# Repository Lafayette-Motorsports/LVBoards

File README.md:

# MotorsportsLVBoards

LV Board repository for Motorsports created 09.02.2025  

## BE SURE TO COMMIT & PUSH ALL CHANGES WHEN FINISHED TO KEEP THINGS UPDATED  

## Modulation
LV Boards are now 'modulated' - this means that each board is designed to serve a single purpose so that individual circuits/functions can be easily replaced  
    This means that wires need to be obviosuly labeled with their purpose and output params/types to keep things 'open source' enough that it can be easily updated -- keep documentation (wiring diagram, code comments, standalone documentation) updated, descriptive, and accurate  

## If this is your first time
To use this and work on the board (non cmd because if you don't know this you don't need to be trying to do it on the console):  
    - make a github account   
        - you can do this with your school email or your personal but if you plan on making changes, make your screen name traceable (eg. we want to be able to know who's doing stuff)  
    - download github for desktop (https://desktop.github.com/download/) and sign in  
    - 'follow' this repository to add it to your account  
    - click current repository (top left) --> add --> clone repository --> pull origin  
    - find your file path (repository --> show in explorer) and open whatever you want  
    - if you make changes, YOU NEED TO MANUALLY UPDATE THE REPOSITORY, ALL CHANGES MADE ARE LOCAL UNTIL THIS IS DONE  
        - go back to your github app and open the repository (its probably still open), add a summary and commit your changes, push to origin  
        - MAKE YOUR SUMMARY SOMEWHAT DETAILED, YOU DON'T NEED A PARAGRAPH BUT THIS IS A REALLY GOOD PLACE TO PUT A CHANGE LOG SO WE CAN TRACK WHATS HAPPENING WHEN AND GET A SOMEWHAT DETAILED HISTORY  

## Component Cacheing
When adding parts, store them as project-specific rather than global. You will need to create your own library for the project, but you should really only need to do it once per KiCad project -- this will make sure that projects are actually portable. Some projects were built without this in mind so be weary when trying to modify/process files -- they might not have footprints/symbols for every part. If you can't figure out how to do this (or you think you added a symbol but it's not working, footprint not loading, etc.) google it or ask -- the whole point of the GitHub is portability so its kind of stupid to ignore this.

for repository admin (or other) questions - Sean McLoughlin mclougsm@lafayette.edu

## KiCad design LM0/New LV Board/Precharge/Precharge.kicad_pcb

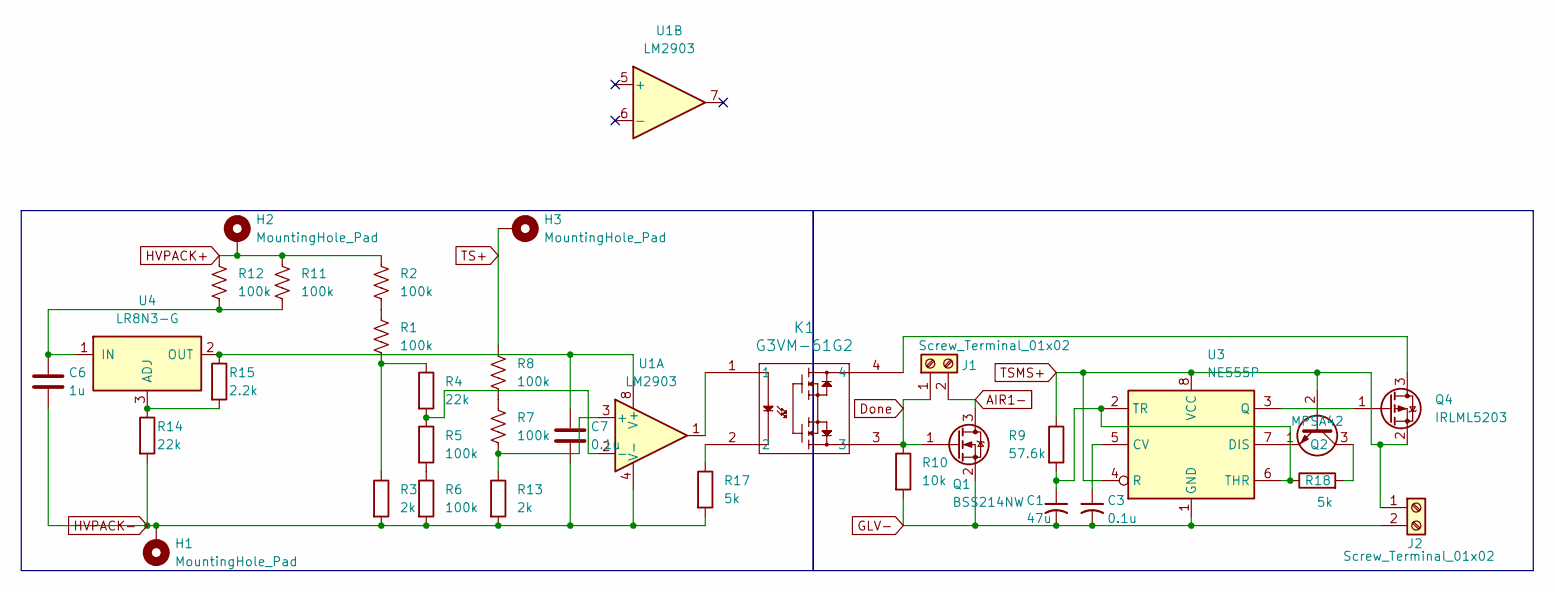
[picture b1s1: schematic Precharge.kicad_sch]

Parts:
C1: 47u; C_1210_3225Metric_Pad1.33x2.70mm_HandSolder
C3, C7: 0.1u; C_1206_3216Metric_Pad1.33x1.80mm_HandSolder
C6: 1u; C_1206_3216Metric_Pad1.33x1.80mm_HandSolder
H1, H2, H3: MountingHole_Pad; MountingHole_5.3mm_M5_DIN965_Pad
J1, J2: Screw_Terminal_01x02; TerminalBlock_MaiXu_MX126-5.0-02P_1x02_P5.00mm
K1: G3VM-61G2; G-SOP4_OMR
Q1: BSS214NW; SOT-323_SC-70_Handsoldering
Q2: MPSA42; TO-92
Q4: IRLML5203; SOT-23_Handsoldering
R1, R2, R7, R8: 100k; R_Axial_DIN0516_L15.5mm_D5.0mm_P5.08mm_Vertical
R3, R13: 2k; R_Axial_DIN0207_L6.3mm_D2.5mm_P2.54mm_Vertical
R4, R14: 22k; R_Axial_DIN0207_L6.3mm_D2.5mm_P2.54mm_Vertical
R5, R6: 100k; R_Axial_DIN0207_L6.3mm_D2.5mm_P2.54mm_Vertical
R9: 57.6k; R_Axial_DIN0207_L6.3mm_D2.5mm_P2.54mm_Vertical
R10: 10k; R_Axial_DIN0207_L6.3mm_D2.5mm_P2.54mm_Vertical
R11, R12: 100k; R_Axial_DIN0516_L15.5mm_D5.0mm_P7.62mm_Vertical
R15: 2.2k; R_Axial_DIN0207_L6.3mm_D2.5mm_P2.54mm_Vertical
R17, R18: 5k; R_Axial_DIN0207_L6.3mm_D2.5mm_P2.54mm_Vertical
U1: LM2903; DIP-8_W7.62mm
U3: NE555P; DIP-8_W7.62mm
U4: LR8N3-G; TO-92

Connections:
AIR1-: J1.2, Q1.3 (D)
Done: J1.1, K1.3, Q1.1 (G), R10.1
GLV-: C1.2, C3.2, J2.2, Q1.2 (S), R10.2, U3.1 (GND)
HVPACK+: H2.1, R2.1, R11.1, R12.1
HVPACK-: C6.2, C7.2, H1.1, R3.2, R6.2, R13.2, R14.2, R17.2, U1.4 (V-)
unnamed: K1.1, U1.1
unnamed: K1.2, R17.1
unnamed: Q2.3 (C), R18.2
unnamed: Q2.1 (E), U3.7 (DIS)
unnamed: K1.4, Q4.3 (D)
unnamed: Q4.1 (G), U3.3 (Q)
unnamed: R1.1, R2.2
unnamed: R1.2, R3.1, R4.1
unnamed: R5.2, R6.1
unnamed: R7.1, R8.2
unnamed: R7.2, R13.1, U1.3 (+)
unnamed: R4.2, R5.1, U1.2 (-)
unnamed: C7.1, R15.1, U1.8 (V+), U4.2 (OUT)
unnamed: C3.1, U3.5 (CV)
unnamed: C1.1, R9.2, R18.1, U3.2 (TR), U3.6 (THR)
unnamed: R14.1, R15.2, U4.3 (ADJ)
unnamed: C6.1, R11.2, R12.2, U4.1 (IN)
TS+: H3.1, R8.1
TSMS+: J2.1, Q2.2 (B), Q4.2 (S), R9.1, U3.4 (R), U3.8 (VCC)

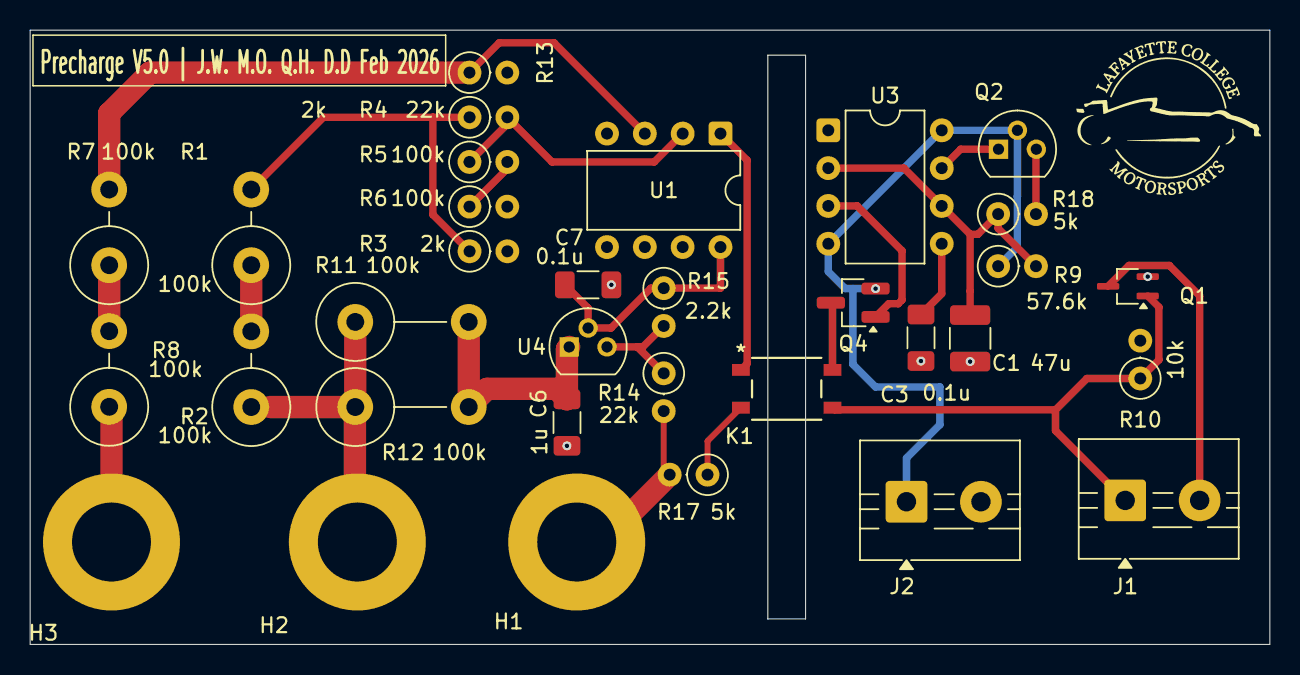
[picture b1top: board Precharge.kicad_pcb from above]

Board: 2 copper layers, 83.2 x 41.2 mm, 33 parts (0 on the bottom side), 24 nets.

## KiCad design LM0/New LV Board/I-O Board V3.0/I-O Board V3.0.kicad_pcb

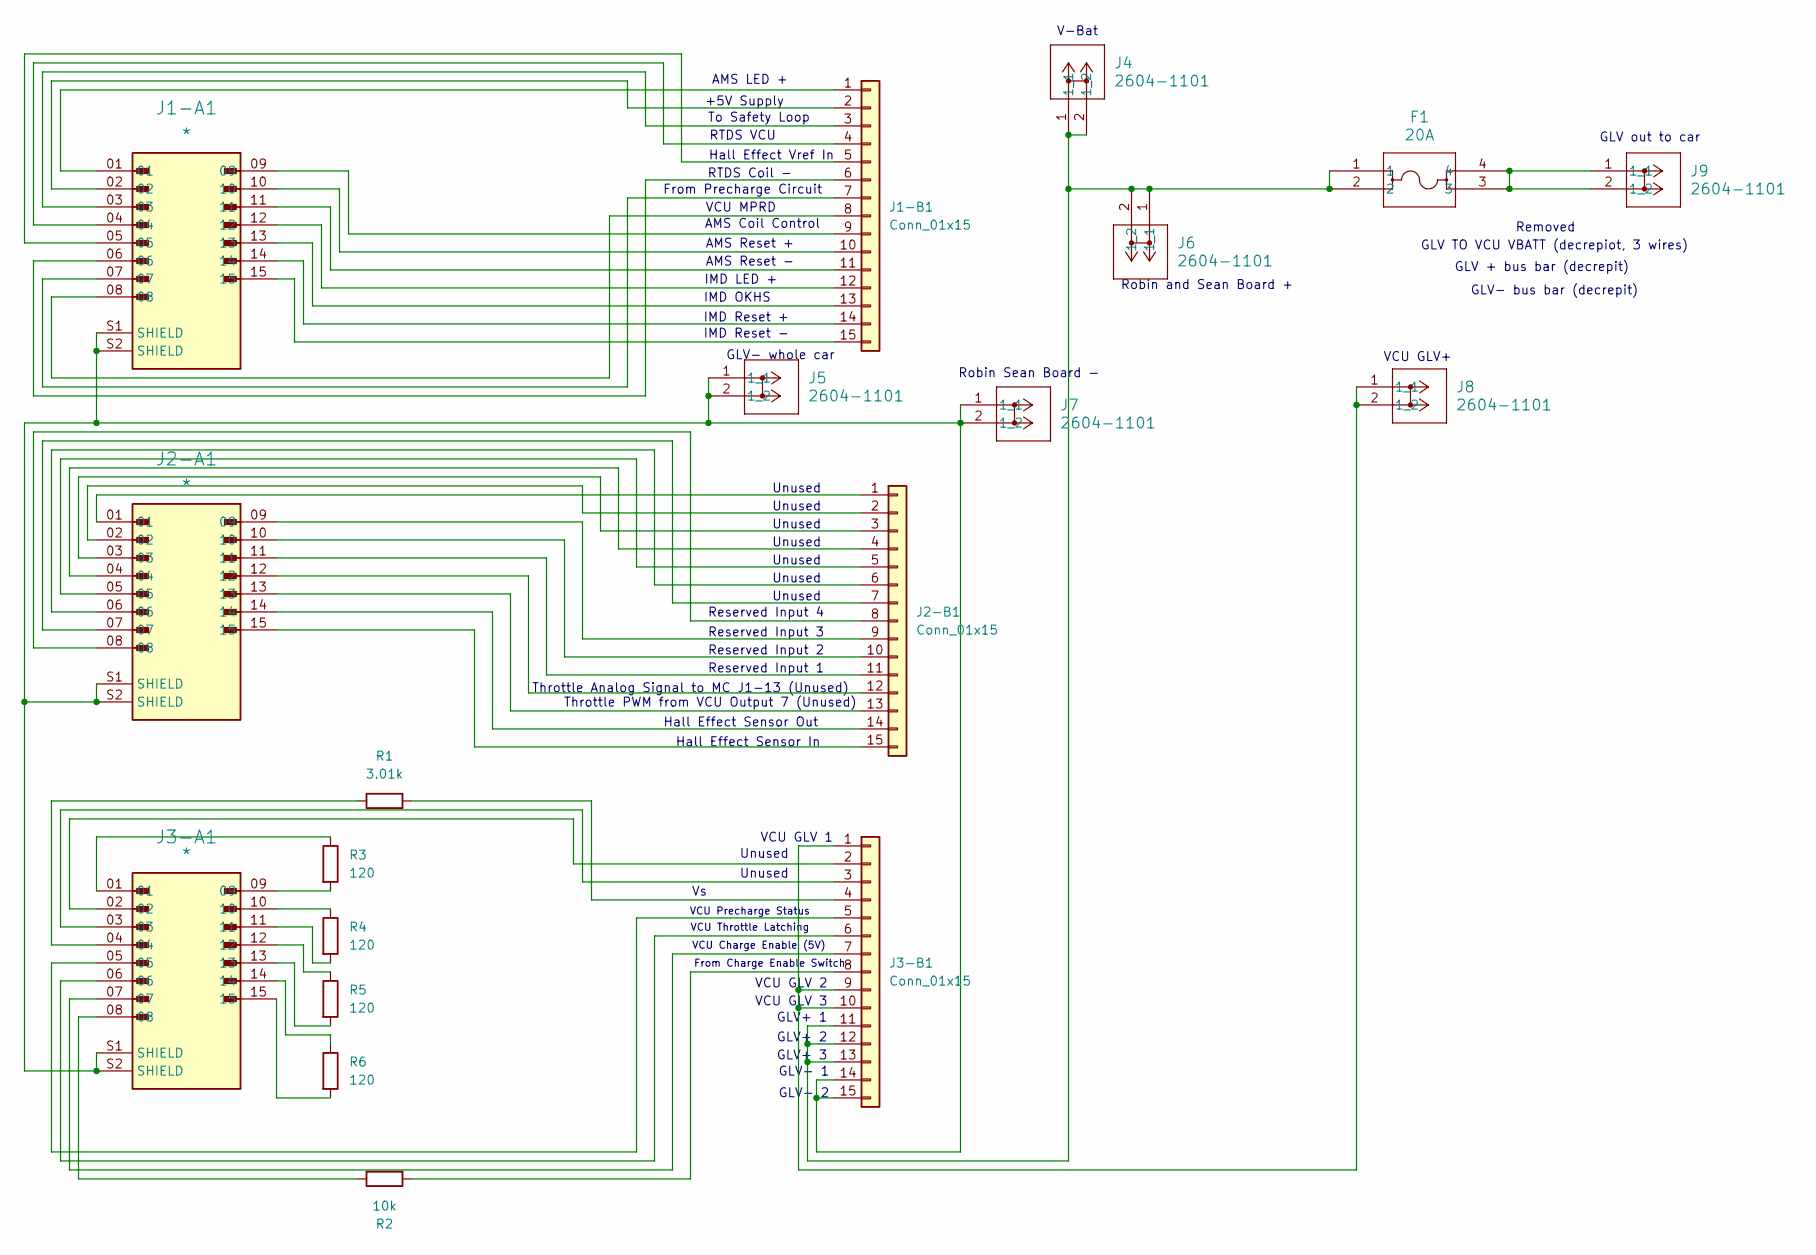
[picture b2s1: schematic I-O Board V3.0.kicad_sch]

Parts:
F1: 20A; 3568_KEY
J1-A1, J2-A1, J3-A1: *; AMPHENOL_L717SDA15P1ACH4F
J1-B1, J2-B1, J3-B1: Conn_01x15; JST_PH_B15B-PH-K_1x15_P2.00mm_Vertical
J4, J5, J6, J7, J8, J9: 2604-1101; CONN_2604-1101_WAG
R1: 3.01k; YAG_MF25_YAG
R2: 10k; YAG_MF25_YAG
R3, R4, R5, R6: 120; RESC3116X65N

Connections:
unnamed: J1-A1.01, J1-B1.1
unnamed: J1-A1.02, J1-B1.2
unnamed: J1-A1.03, J1-B1.3
unnamed: J1-A1.04, J1-B1.4
unnamed: J1-A1.05, J1-B1.5
unnamed: J1-A1.06, J1-B1.6
unnamed: J1-A1.07, J1-B1.7
unnamed: J1-A1.08, J1-B1.8
unnamed: J1-A1.09, J1-B1.9
unnamed: J1-A1.10, J1-B1.10
unnamed: J1-A1.11, J1-B1.11
unnamed: J1-A1.12, J1-B1.12
unnamed: J1-A1.13, J1-B1.13
unnamed: J1-A1.14, J1-B1.14
unnamed: J1-A1.15, J1-B1.15
unnamed: J2-A1.01, J2-B1.1
unnamed: J2-A1.02, J2-B1.2
unnamed: J2-A1.03, J2-B1.3
unnamed: J2-A1.04, J2-B1.4
unnamed: J2-A1.05, J2-B1.5
unnamed: J2-A1.06, J2-B1.6
unnamed: J2-A1.07, J2-B1.7
unnamed: J2-A1.08, J2-B1.8
unnamed: J2-A1.09, J2-B1.9
unnamed: J2-A1.10, J2-B1.10
unnamed: J2-A1.11, J2-B1.11
unnamed: J2-A1.12, J2-B1.12
unnamed: J2-A1.13, J2-B1.13
unnamed: J2-A1.14, J2-B1.14
unnamed: J2-A1.15, J2-B1.15
unnamed: J3-A1.01, R3.1
unnamed: J3-A1.04, R1.1
unnamed: J3-A1.08, R2.1
unnamed: J3-A1.09, R3.2
unnamed: J3-A1.10, R4.1
unnamed: J3-A1.11, R4.2
unnamed: J3-A1.12, R5.1
unnamed: J3-A1.13, R5.2
unnamed: J3-A1.14, R6.1
unnamed: J3-A1.15, R6.2
unnamed: J3-B1.1, J3-B1.9, J3-B1.10, J8.1, J8.2 (1)
unnamed: J3-A1.02, J3-B1.2
unnamed: J3-A1.03, J3-B1.3
unnamed: J3-B1.4, R1.2
unnamed: J3-A1.05, J3-B1.5
unnamed: J3-A1.06, J3-B1.6
unnamed: J3-A1.07, J3-B1.7
unnamed: J3-B1.8, R2.2
unnamed: F1.1, F1.2, J3-B1.11, J3-B1.12, J3-B1.13, J4.1, J4.2 (1), J6.1, J6.2 (1)
unnamed: J1-A1.S1 (SHIELD), J1-A1.S2 (SHIELD), J2-A1.S1 (SHIELD), J2-A1.S2 (SHIELD), J3-A1.S1 (SHIELD), J3-A1.S2 (SHIELD), J3-B1.14, J3-B1.15, J5.1, J5.2 (1), J7.1, J7.2 (1)
unnamed: F1.3, F1.4, J9.1, J9.2 (1)

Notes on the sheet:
V-Bat
AMS LED +
+5V Supply
VCU GLV 2
Unused
Reserved Input 2
IMD Reset -
IMD Reset +
VCU MPRD
GLV+ 3
IMD OKHS
Reserved Input 1
GLV+ 2
RTDS Coil -
VCU Charge Enable (5V)
GLV- whole car
Unused
GLV + bus bar (decrepit)
To Safety Loop
Removed
VCU GLV+
Robin Sean Board -
GLV- bus bar (decrepit)
Hall Effect Sensor Out
GLV- 1
Hall Effect Vref In
AMS Coil Control
From Charge Enable Switch
AMS Reset +
Robin and Sean Board +
GLV- 2
GLV TO VCU VBATT (decrepiot, 3 wires)
VCU GLV 1
Throttle PWM from VCU Output 7 (Unused)
Hall Effect Sensor In
VCU GLV 3
Throttle Analog Signal to MC J1-13 (Unused)
From Precharge Circuit
VCU Throttle Latching
Reserved Input 3

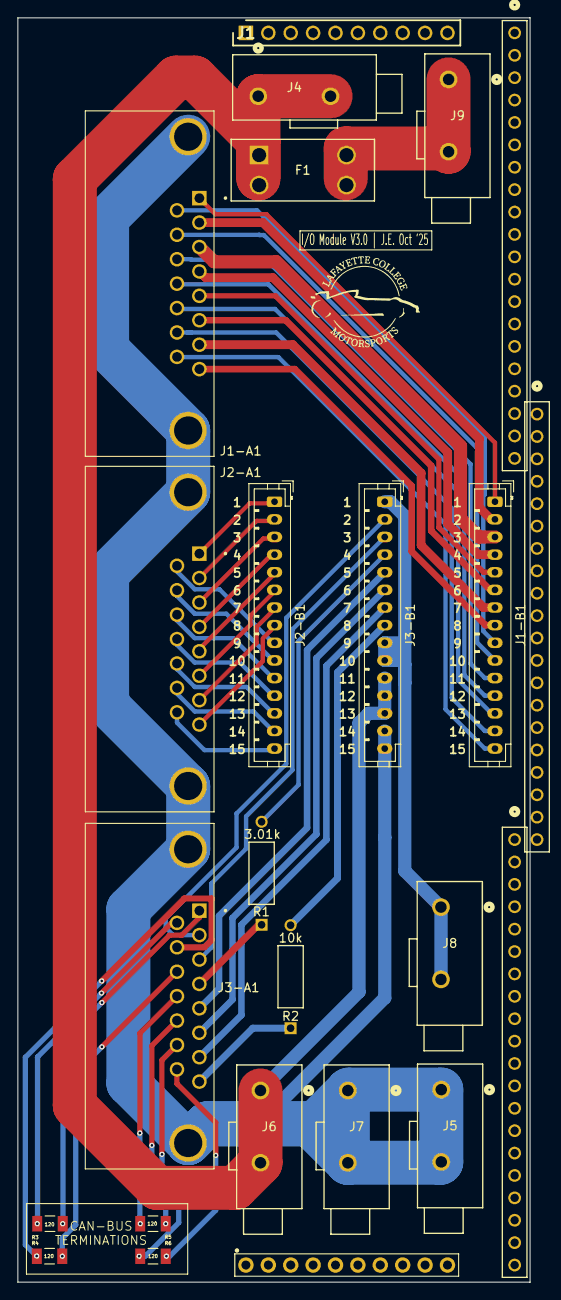
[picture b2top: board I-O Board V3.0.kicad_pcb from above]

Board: 2 copper layers, 58.1 x 143.4 mm, 24 parts (0 on the bottom side), 51 nets.

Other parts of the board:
J1: PH1-10-UA; HDRV10W64P0X254_1X10_2540X249X886P
PH2, PH2#2, PH3: 20-0600-21; CONN_20-0600-21_ARS
PH4: 1X10-2.54MM-THT

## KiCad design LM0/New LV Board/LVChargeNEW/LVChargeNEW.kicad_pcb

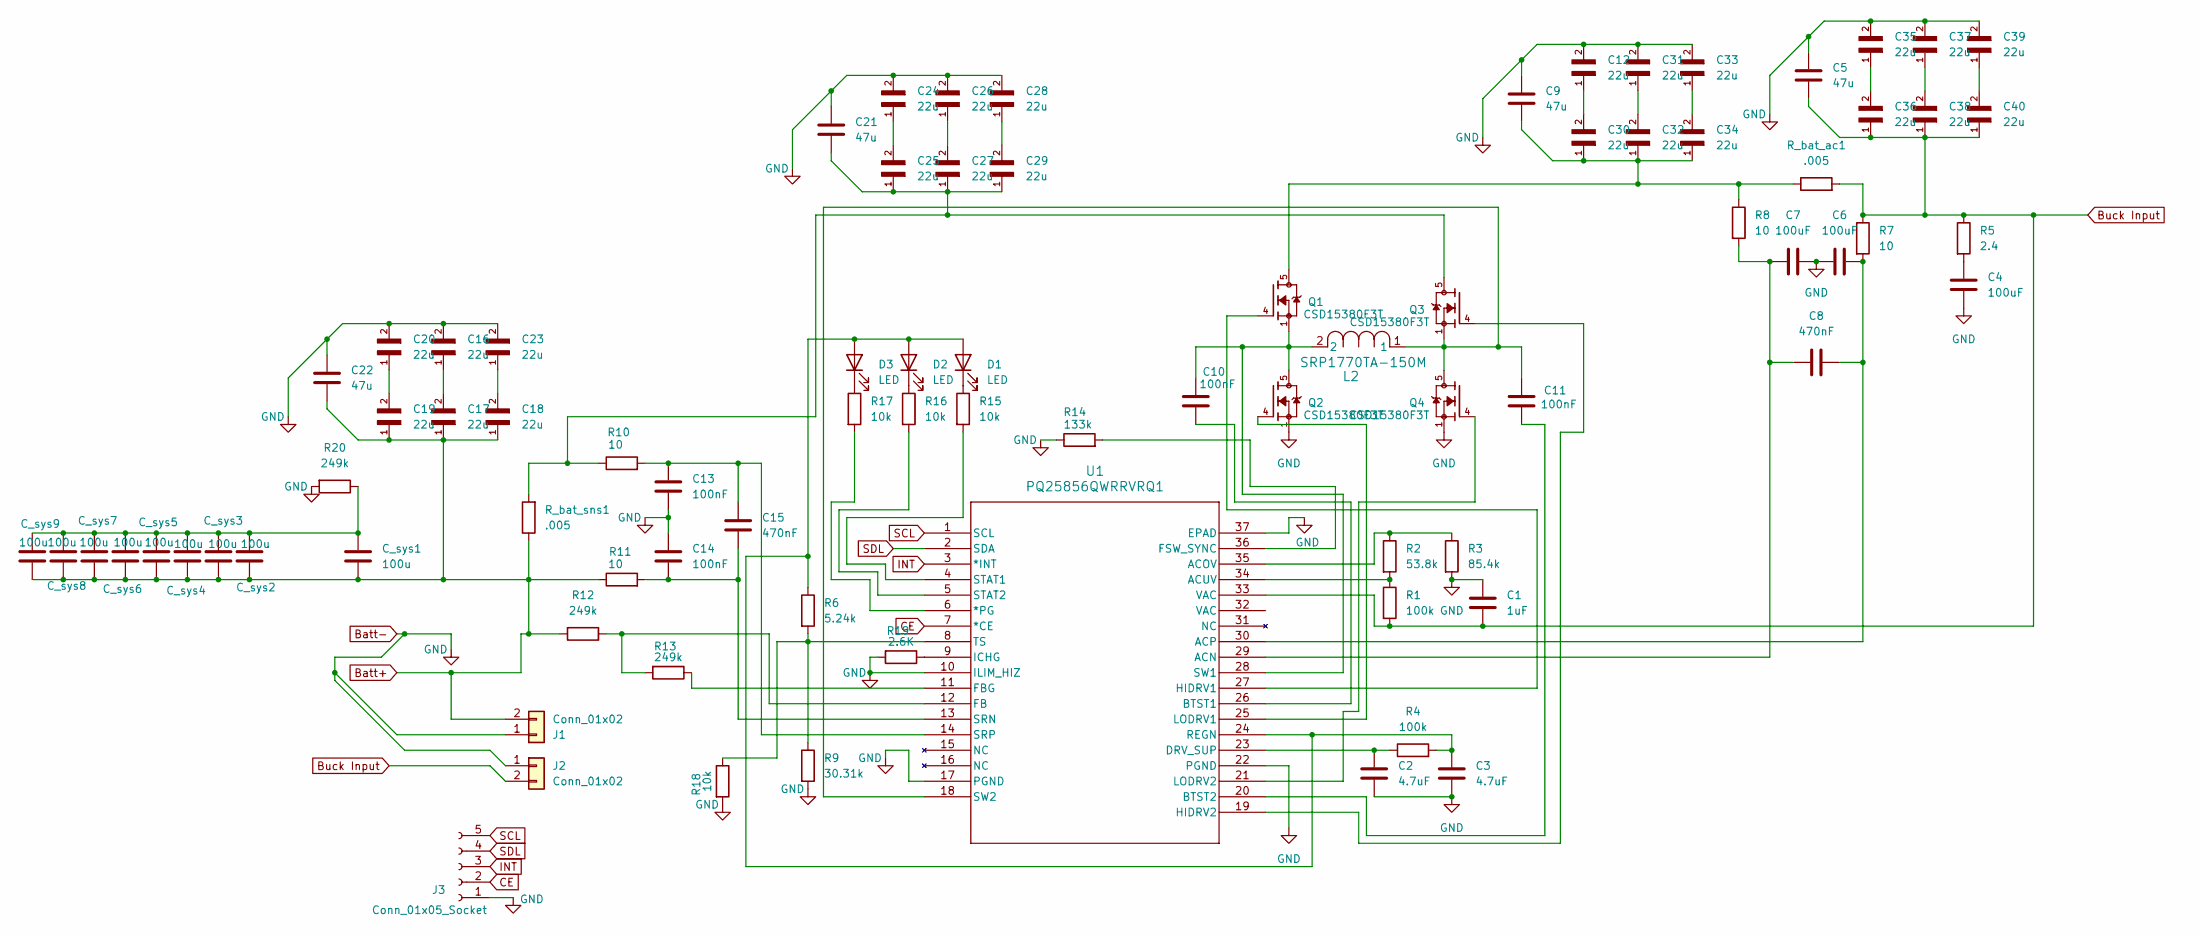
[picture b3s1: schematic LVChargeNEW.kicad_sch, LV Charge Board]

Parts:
C1: 1uF; CP_Radial_D8.0mm_P5.00mm
C2, C3: 4.7uF; CP_Radial_D8.0mm_P5.00mm
C4, C6, C7: 100uF; CP_Radial_D8.0mm_P5.00mm
C5, C9, C21, C22: 47u; C_1210_3225Metric
C8, C15: 470nF; CP_Radial_D8.0mm_P5.00mm
C10, C11, C13, C14: 100nF; CP_Radial_D8.0mm_P5.00mm
C12, C16, C17, C18, C19, C20, C23, C24, C25, C26, C27, C28, C29, C30, C31, C32, C33, C34, C35, C36, C37, C38, C39, C40: 22u; C_1210_3225Metric
C_sys1, C_sys2, C_sys3, C_sys4, C_sys5, C_sys6, C_sys7, C_sys8, C_sys9: 100u; C_1210_3225Metric_Pad1.33x2.70mm_HandSolder
D1, D2, D3: LED; LED_1206_3216Metric
J1, J2: Conn_01x02; TerminalBlock_Altech_AK300-2_P5.00mm
J3: Conn_01x05_Socket; PinSocket_1x06_P1.27mm_Vertical
L2: SRP1770TA-150M; SRP1770TA_150M
Q1, Q2, Q3, Q4: CSD15380F3T; IAUZ20N08S5L300ATMA1; PARTREV A
R1, R4: 100k; R_Axial_DIN0204_L3.6mm_D1.6mm_P5.08mm_Horizontal
R2: 53.8k; R_0805_2012Metric
R3: 85.4k; R_1206_3216Metric
R5: 2.4; R_1206_3216Metric
R6: 5.24k; R_0402_1005Metric
R7, R8, R10, R11: 10; R_1206_3216Metric_Pad1.30x1.75mm_HandSolder
R9: 30.31k; R_0805_2012Metric
R12, R13, R20: 249k; R_Axial_DIN0204_L3.6mm_D1.6mm_P5.08mm_Horizontal
R14: 133k; R_Axial_DIN0204_L3.6mm_D1.6mm_P5.08mm_Horizontal
R15, R16, R17, R18: 10k; R_Axial_DIN0204_L3.6mm_D1.6mm_P5.08mm_Horizontal
R19: 2.6K; R_0402_1005Metric_Pad0.72x0.64mm_HandSolder
R_bat_ac1: .005; RESC2012X80N
R_bat_sns1: .005; RESC2012X80N
U1: PQ25856QWRRVRQ1; Q25856QWRRVRQ1

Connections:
Batt+: C17.1, C18.1, C19.1, C22.2, C_sys1.2, C_sys2.2, C_sys3.2, C_sys4.2, C_sys5.2, C_sys6.2, C_sys7.2, C_sys8.2, C_sys9.2, J1.2, R11.1, R12.2, R_bat_sns1.1
Batt-: C1.1, C2.2, C3.2, C4.2, C5.1, C6.1, C7.2, C9.1, C12.2, C13.2, C14.1, C16.2, C20.2, C21.1, C22.1, C23.2, C24.2, C26.2, C28.2, C31.2, C33.2, C35.2, C37.2, C39.2, J1.1, J2.1, J3.1, Q2.1, Q4.1, R3.2, R9.2, R14.1, R18.2, R19.2, R20.2, U1.10 (ILIM_HIZ), U1.17 (PGND), U1.22 (PGND), U1.37 (EPAD)
Buck Input: C1.2, C5.2, C36.1, C38.1, C40.1, J2.2, R1.2, R5.1, R7.1, R_bat_ac1.2, U1.33 (VAC)
CE: J3.2, U1.7 (*CE)
INT: J3.3, U1.3 (*INT)
unnamed: C4.1, R5.2
unnamed: C12.1, C30.2
unnamed: C16.1, C17.2
unnamed: C18.2, C23.1
unnamed: C19.2, C20.1
unnamed: C21.2, C25.1, C27.1, C29.1, Q3.5, R10.1, R_bat_sns1.2
unnamed: C24.1, C25.2
unnamed: C26.1, C27.2
unnamed: C28.1, C29.2
unnamed: C9.2, C30.1, C32.1, C34.1, Q1.5, R8.1, R_bat_ac1.1
unnamed: C31.1, C32.2
unnamed: C33.1, C34.2
unnamed: C35.1, C36.2
unnamed: C37.1, C38.2
unnamed: C39.1, C40.2
unnamed: C_sys1.1, C_sys2.1, C_sys3.1, C_sys4.1, C_sys5.1, C_sys6.1, C_sys7.1, C_sys8.1, C_sys9.1, R20.1
unnamed: C3.1, D1.2 (A), D2.2 (A), D3.2 (A), R4.2, R6.1, U1.24 (REGN)
unnamed: D1.1 (K), R15.1
unnamed: D2.1 (K), R16.1
unnamed: D3.1 (K), R17.1
unnamed: R17.2, U1.6 (*PG)
unnamed: C7.1, C8.1, R8.2, U1.29 (ACN)
unnamed: R2.1, R3.1, U1.35 (ACOV)
unnamed: C6.2, C8.2, R7.2, U1.30 (ACP)
unnamed: R1.1, R2.2, U1.34 (ACUV)
unnamed: C10.1, U1.26 (BTST1)
unnamed: C11.1, U1.20 (BTST2)
unnamed: C2.1, R4.1, U1.23 (DRV_SUP)
unnamed: R12.1, R13.2, U1.12 (FB)
unnamed: R13.1, U1.11 (FBG)
unnamed: R14.2, U1.36 (FSW_SYNC)
unnamed: Q1.4, U1.27 (HIDRV1)
unnamed: Q3.4, U1.19 (HIDRV2)
unnamed: R19.1, U1.9 (ICHG)
unnamed: Q2.4, U1.25 (LODRV1)
unnamed: Q4.4, U1.21 (LODRV2)
unnamed: C14.2, C15.2, R11.2, U1.13 (SRN)
unnamed: C13.1, C15.1, R10.2, U1.14 (SRP)
unnamed: R15.2, U1.4 (STAT1)
unnamed: R16.2, U1.5 (STAT2)
unnamed: C10.2, L2.2, Q1.1, Q2.5, U1.28 (SW1)
unnamed: C11.2, L2.1, Q3.1, Q4.5, U1.18 (SW2)
unnamed: R6.2, R9.1, R18.1, U1.8 (TS)
SCL: J3.5, U1.1 (SCL)
SDL: J3.4, U1.2 (SDA)

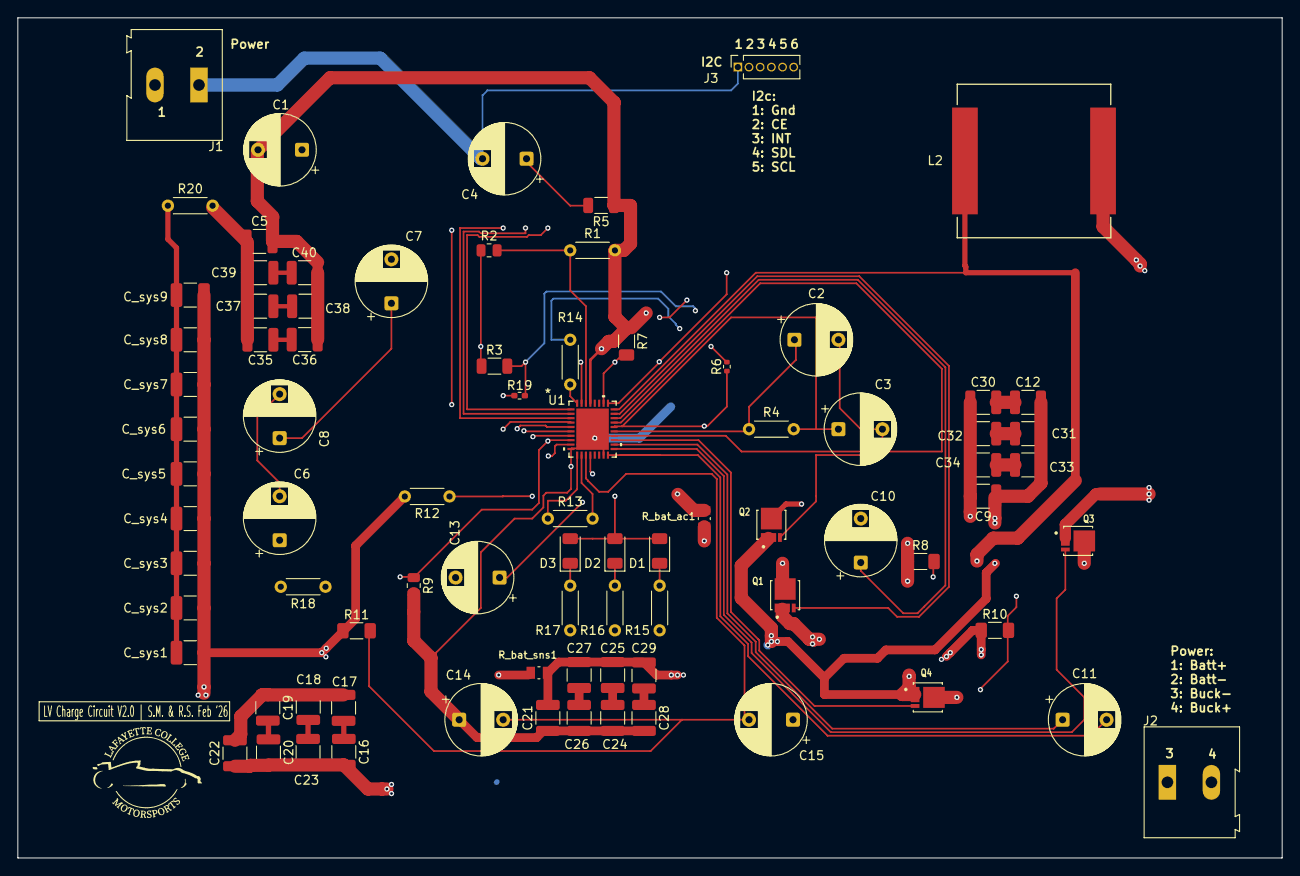
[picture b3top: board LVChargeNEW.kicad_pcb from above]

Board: 4 copper layers, 143.7 x 95.5 mm, 83 parts (0 on the bottom side), 50 nets.

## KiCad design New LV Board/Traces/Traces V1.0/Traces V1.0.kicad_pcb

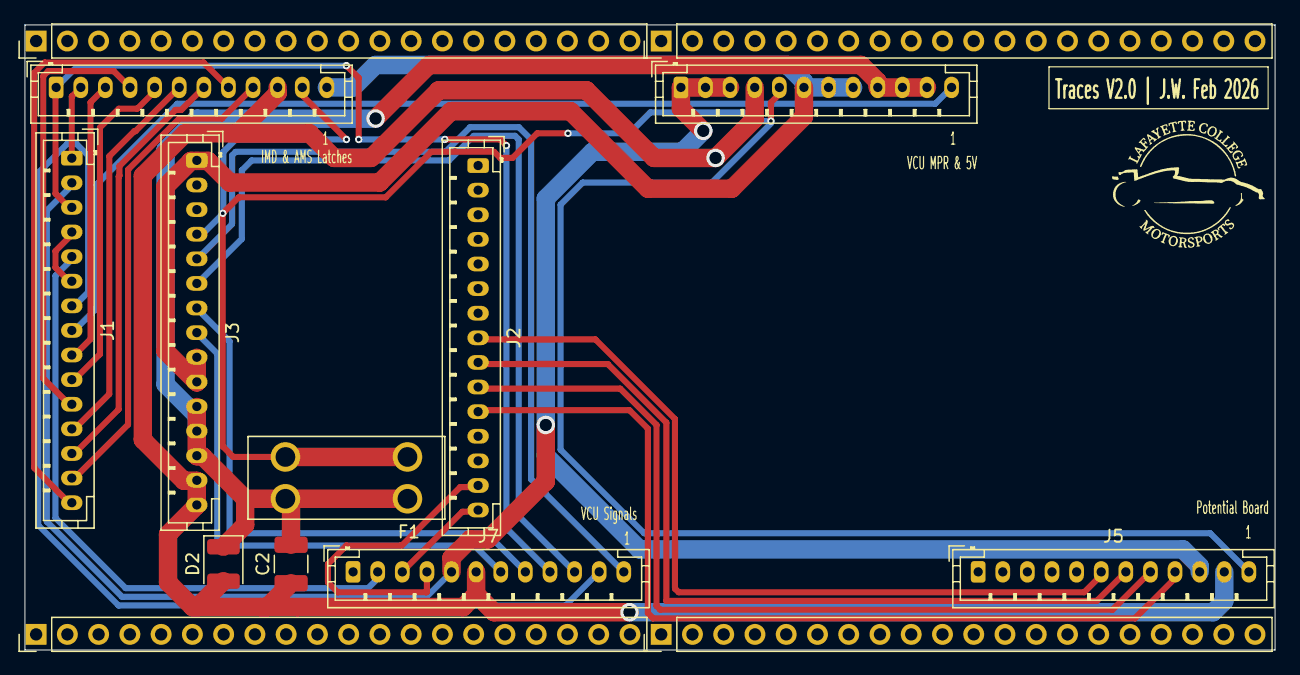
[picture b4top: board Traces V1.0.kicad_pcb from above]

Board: 2 copper layers, 101.6 x 50.8 mm, 10 parts (0 on the bottom side), 28 nets.

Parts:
C2: 47u; C_1210_3225Metric_Pad1.33x2.70mm_HandSolder
D2: D_Zener; D_1210_3225Metric
F1: 2A; FUSE_3568
J1, J2, J3: B15B-PH-K-S; JST_PH_B15B-PH-K_1x15_P2.00mm_Vertical
J4, J5, J6, J7: B12B-PH-K-S; JST_PH_B12B-PH-K_1x12_P2.00mm_Vertical

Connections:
unnamed: C2.1, D2.2 (A), J3.1, J3.2, J4.4, J5.11, J6.10, J7.6
unnamed: C2.2, D2.1 (K), F1.1, F1.2, J3.3, J3.4, J3.5, J4.9, J4.10, J4.11
unnamed: J1.10, J1.12
unnamed: J1.14, J4.1, J4.2, J4.3, J5.10, J7.5
unnamed: F1.3, F1.4, J3.12, J4.5, J5.12, J6.11
unnamed: J3.6, J3.7, J3.15, J4.6, J4.7, J4.8, J6.12
unnamed: J1.8, J4.12
unnamed: J2.8, J5.6
unnamed: J2.7, J5.7
unnamed: J2.6, J5.8
unnamed: J2.5, J5.9
unnamed: J1.13, J6.1, J7.9
unnamed: J1.15, J6.2
unnamed: J1.7, J6.3
unnamed: J1.5, J6.4
unnamed: J1.6, J6.5
unnamed: J1.4, J6.6
unnamed: J1.3, J6.7
unnamed: J1.1, J6.8
unnamed: J1.2, J6.9
unnamed: J1.11, J7.2
unnamed: J2.1, J7.3
unnamed: J2.2, J7.4
unnamed: J3.8, J7.7
unnamed: J3.9, J7.8
unnamed: J3.10, J7.10
unnamed: J1.9, J7.11
unnamed: J3.11, J7.12

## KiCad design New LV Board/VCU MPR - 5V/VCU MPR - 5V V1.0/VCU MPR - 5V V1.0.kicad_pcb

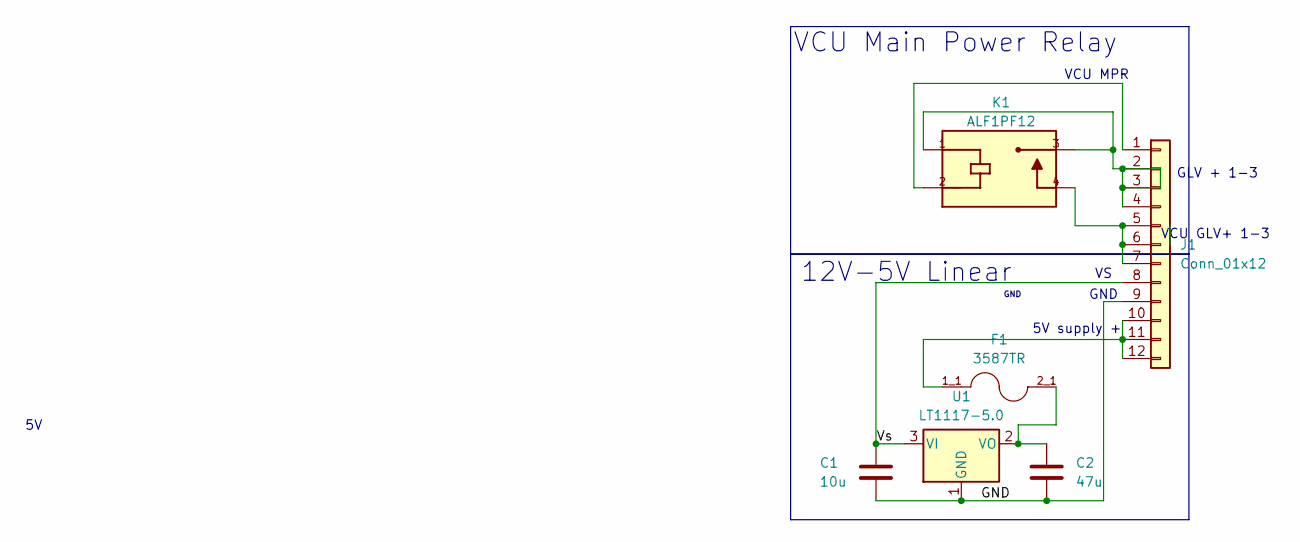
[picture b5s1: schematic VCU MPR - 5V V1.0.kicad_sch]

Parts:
C1: 10u; CAPC3225X270N
C2: 47u; CAPC3225X270N
F1: 3587TR; FUSE_3587; PARTREV D
J1: Conn_01x12; JST_PH_B12B-PH-K_1x12_P2.00mm_Vertical
K1: ALF1PF12; RELAY_ALF1PF12; DigiKey_Part_Number 255-4094-ND
U1: LT1117-5.0; REG_LT1117CST-5_TRPBF

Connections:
/GND: C1.2, C2.2, J1.9, U1.1 (GND)
/Vs: C1.1, J1.8, U1.3 (VI)
unnamed: J1.1, K1.2
unnamed: J1.2, J1.3, J1.4, K1.1, K1.3
unnamed: J1.5, J1.6, J1.7, K1.4
unnamed: F1.1_1, J1.10, J1.11, J1.12
unnamed: C2.1, F1.2_1, U1.2 (VO)

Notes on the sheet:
VCU Main Power Relay
12V-5V Linear
VCU MPR
GLV + 1-3
GND
5V supply +
VCU GLV+ 1-3

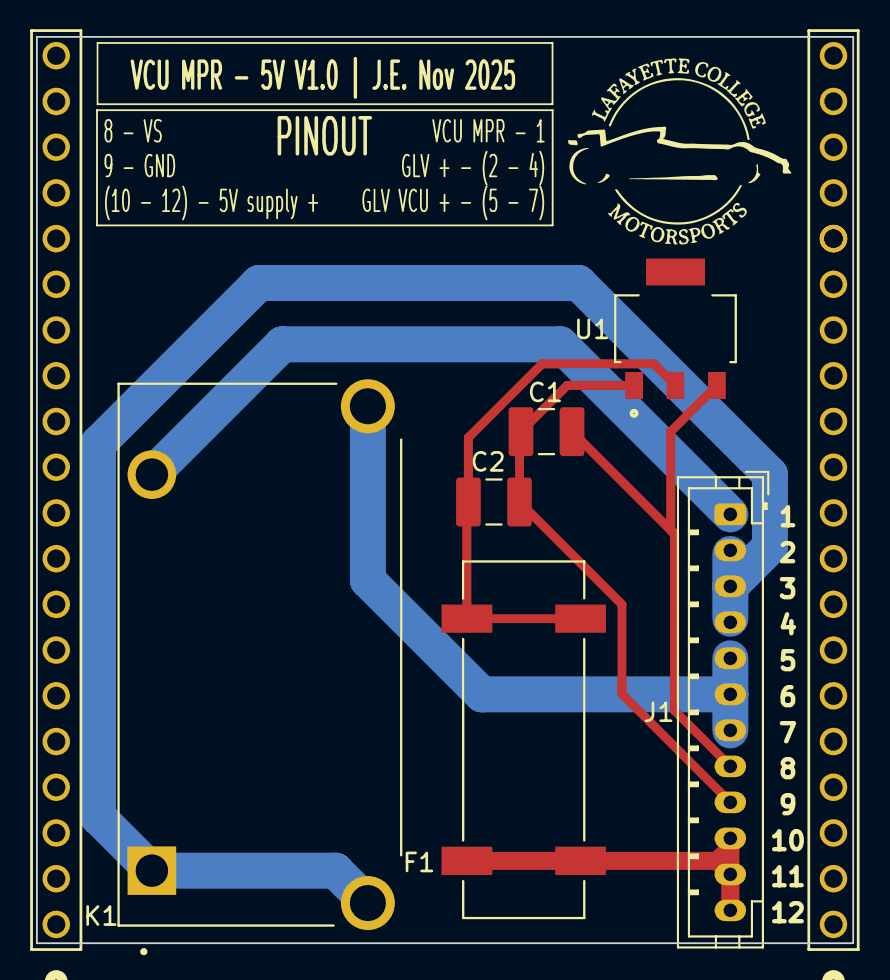
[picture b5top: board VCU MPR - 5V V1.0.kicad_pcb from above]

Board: 2 copper layers, 45.3 x 50.3 mm, 8 parts (0 on the bottom side), 7 nets.

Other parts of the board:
P1, P2: PH1-20-UA; CONN_PH1-20-UA_ADM

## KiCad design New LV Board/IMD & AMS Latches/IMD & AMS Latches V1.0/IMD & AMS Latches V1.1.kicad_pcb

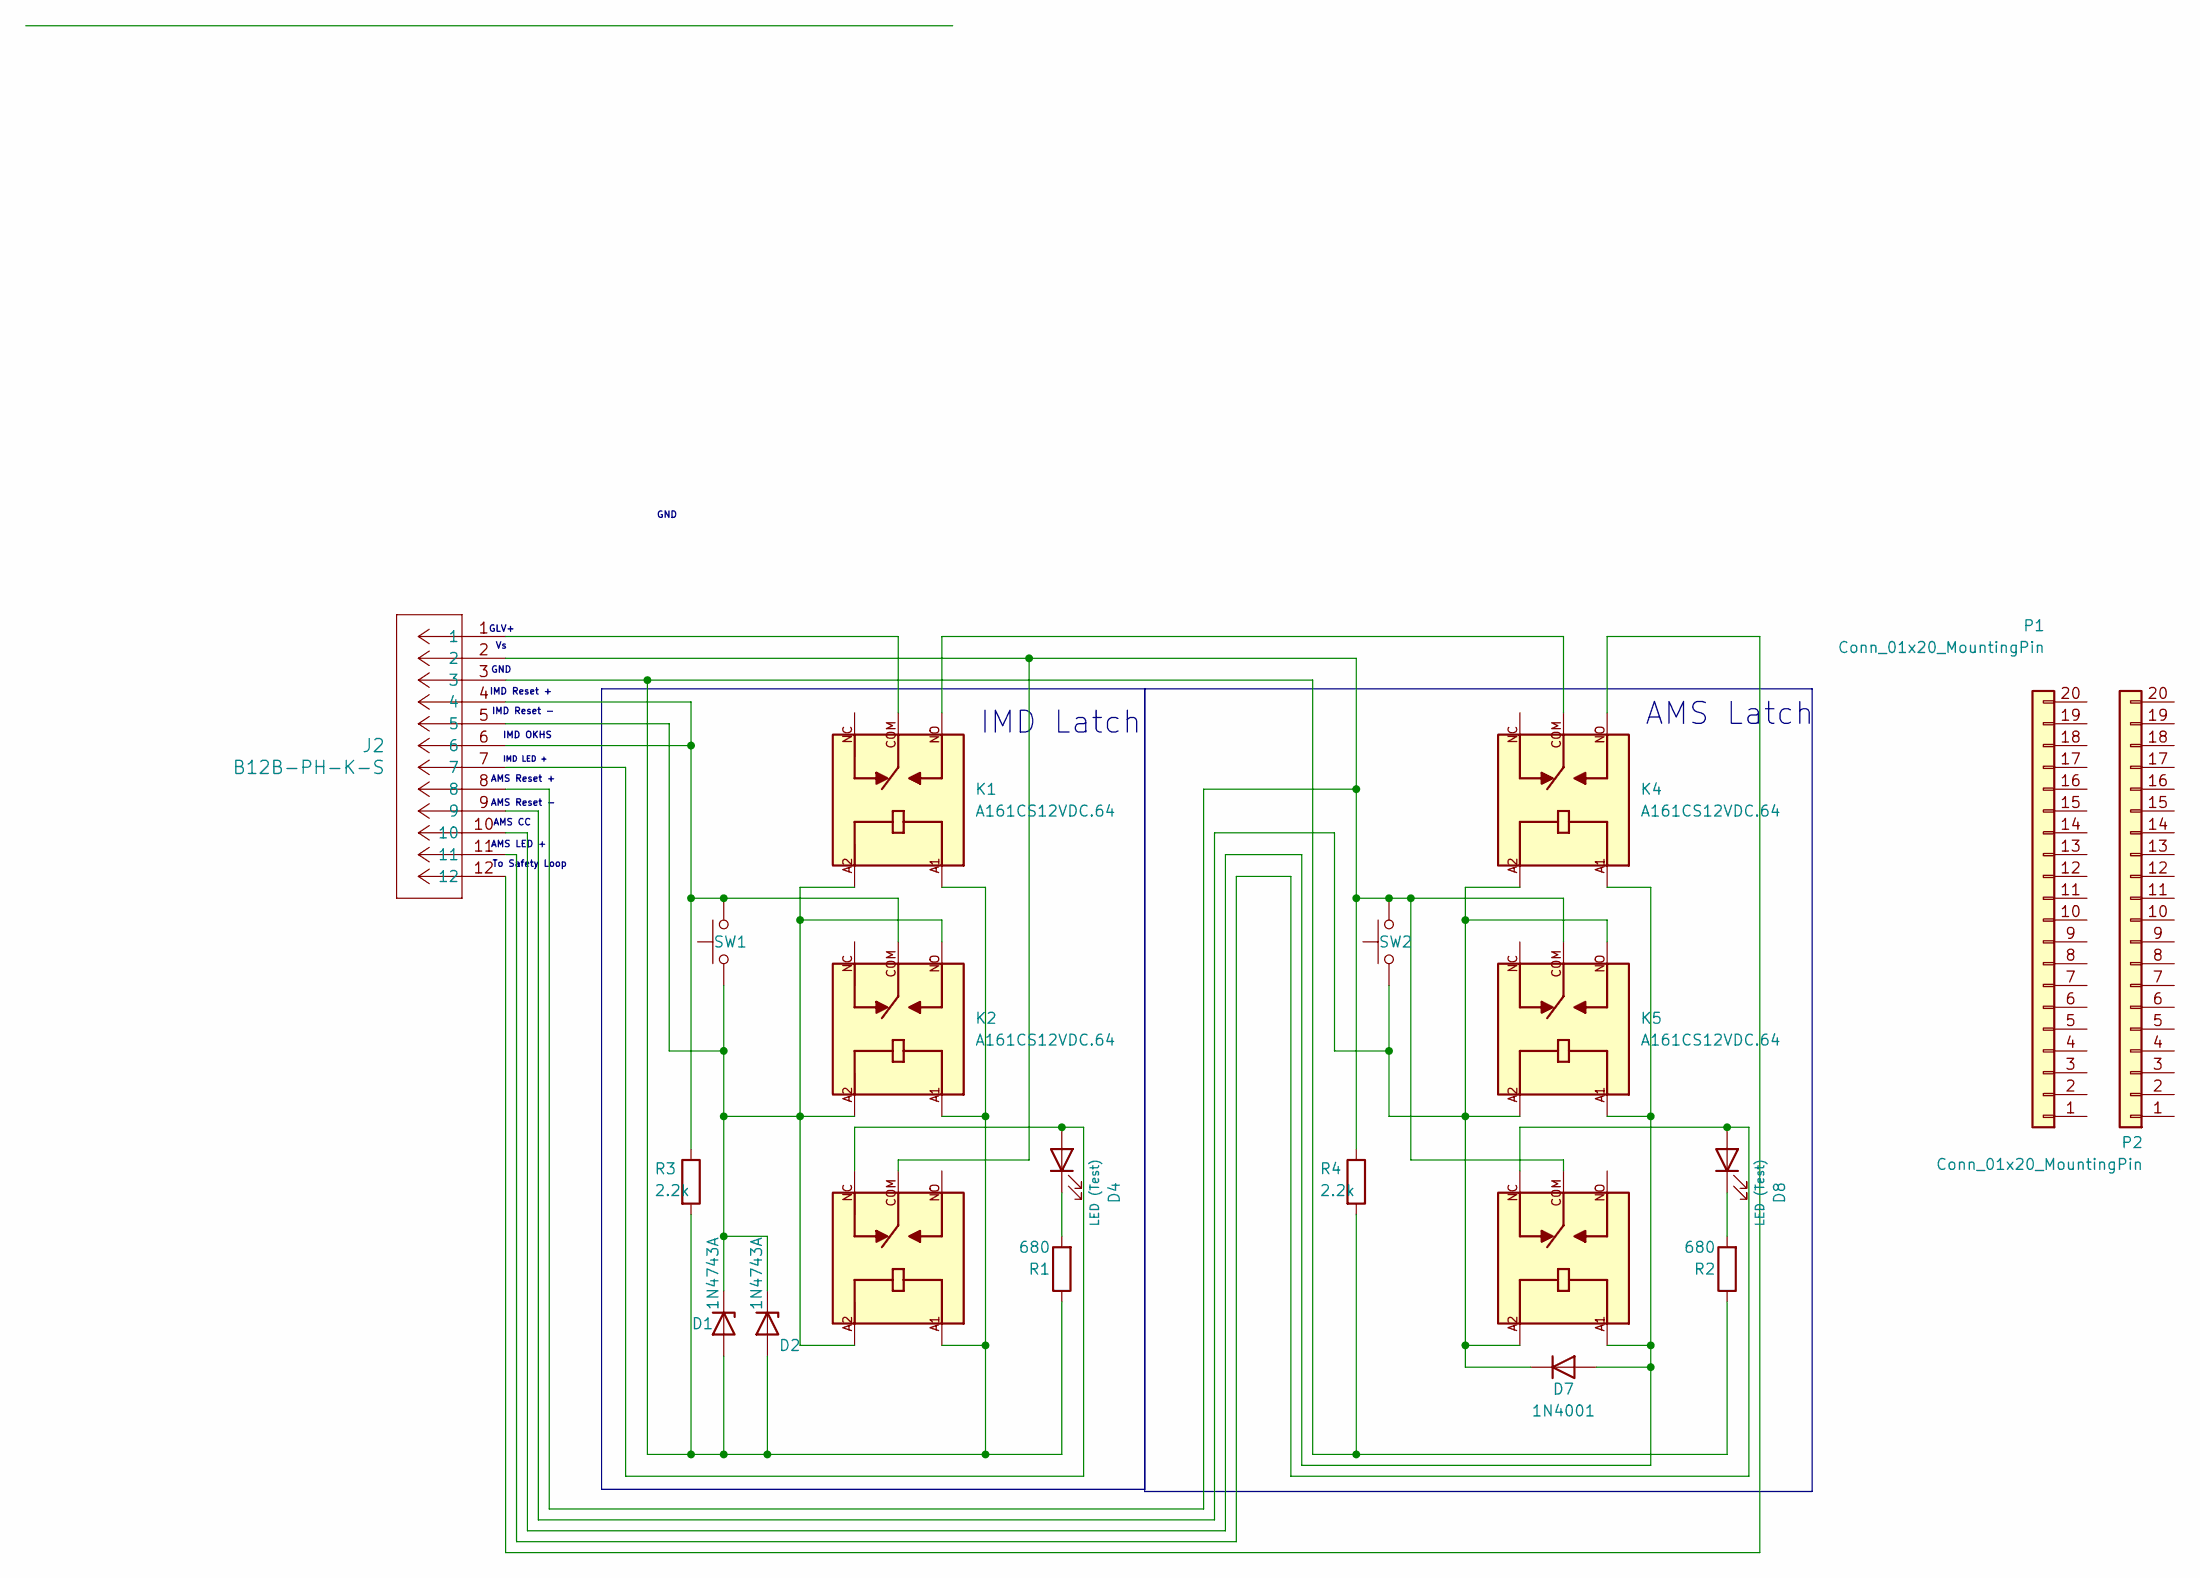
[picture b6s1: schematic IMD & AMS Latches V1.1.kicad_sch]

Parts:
D1, D2: 1N4743A; D_DO-41_SOD81_P3.81mm_Vertical_AnodeUp; Part # 1N4743A
D4, D8: LED (Test); LED_D3.0mm
D7: 1N4001; D_DO-41_SOD81_P10.16mm_Horizontal; Part # 1N4001
J2: B12B-PH-K-S; JST_PH_B12B-PH-K_1x12_P2.00mm_Vertical
K1, K2, K3, K4, K5, K6: A161CS12VDC.64; RELAY_A161CS12VDC.64
P1, P2: Conn_01x20_MountingPin; PinHeader_1x20_P2.54mm_Vertical
R1, R2: 680; R_Axial_DIN0207_L6.3mm_D2.5mm_P2.54mm_Vertical
R3, R4: 2.2k; R_Axial_DIN0207_L6.3mm_D2.5mm_P2.54mm_Vertical
SW1, SW2: Test Reset IMD; pushButton

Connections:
unnamed: D1.2 (A), D2.2 (A), J2.3, K1.A1, K2.A1, K3.A1, R1.1, R2.1, R3.2, R4.2
unnamed: D1.1 (K), D2.1 (K), J2.5, K1.A2, K2.A2, K2.NO, K3.A2, SW1.1
unnamed: D4.2 (A), J2.7, K3.NC
unnamed: D4.1 (K), R1.2
unnamed: D7.2 (A), J2.10, K4.A1, K5.A1, K6.A1
unnamed: D7.1 (K), J2.9, K4.A2, K5.A2, K5.NO, K6.A2, SW2.1
unnamed: D8.2 (A), J2.11, K6.NC
unnamed: D8.1 (K), R2.2
unnamed: J2.1, K1.COM
unnamed: J2.2, J2.8, K3.COM, K5.COM, K6.COM, R4.1, SW2.2
unnamed: J2.4, J2.6, K2.COM, R3.1, SW1.2
unnamed: J2.12, K4.NO
unnamed: K1.NO, K4.COM

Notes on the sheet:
AMS Reset -
IMD OKHS
IMD Reset -
IMD LED +
To Safety Loop
AMS LED +
AMS Reset +
GND
AMS Latch
IMD Reset +
IMD Latch
AMS CC
GLV+

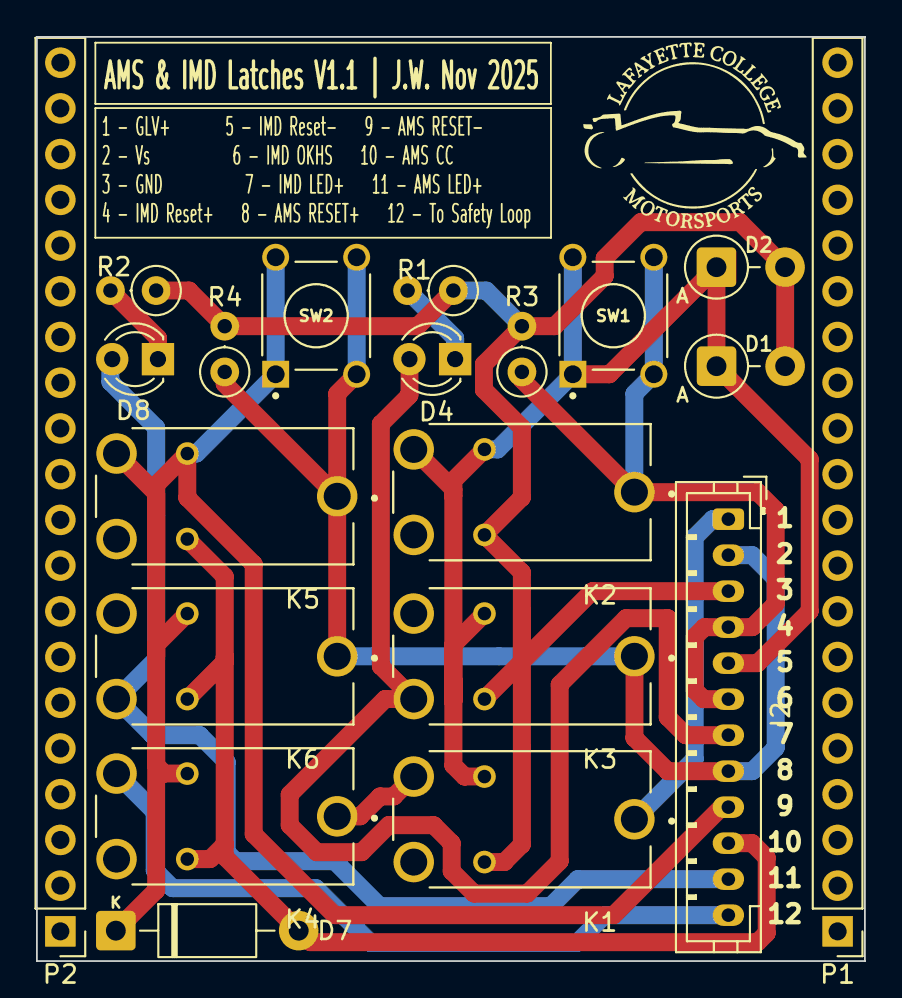
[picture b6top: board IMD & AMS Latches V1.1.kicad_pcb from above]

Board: 2 copper layers, 46.0 x 51.3 mm, 20 parts (0 on the bottom side), 13 nets.
